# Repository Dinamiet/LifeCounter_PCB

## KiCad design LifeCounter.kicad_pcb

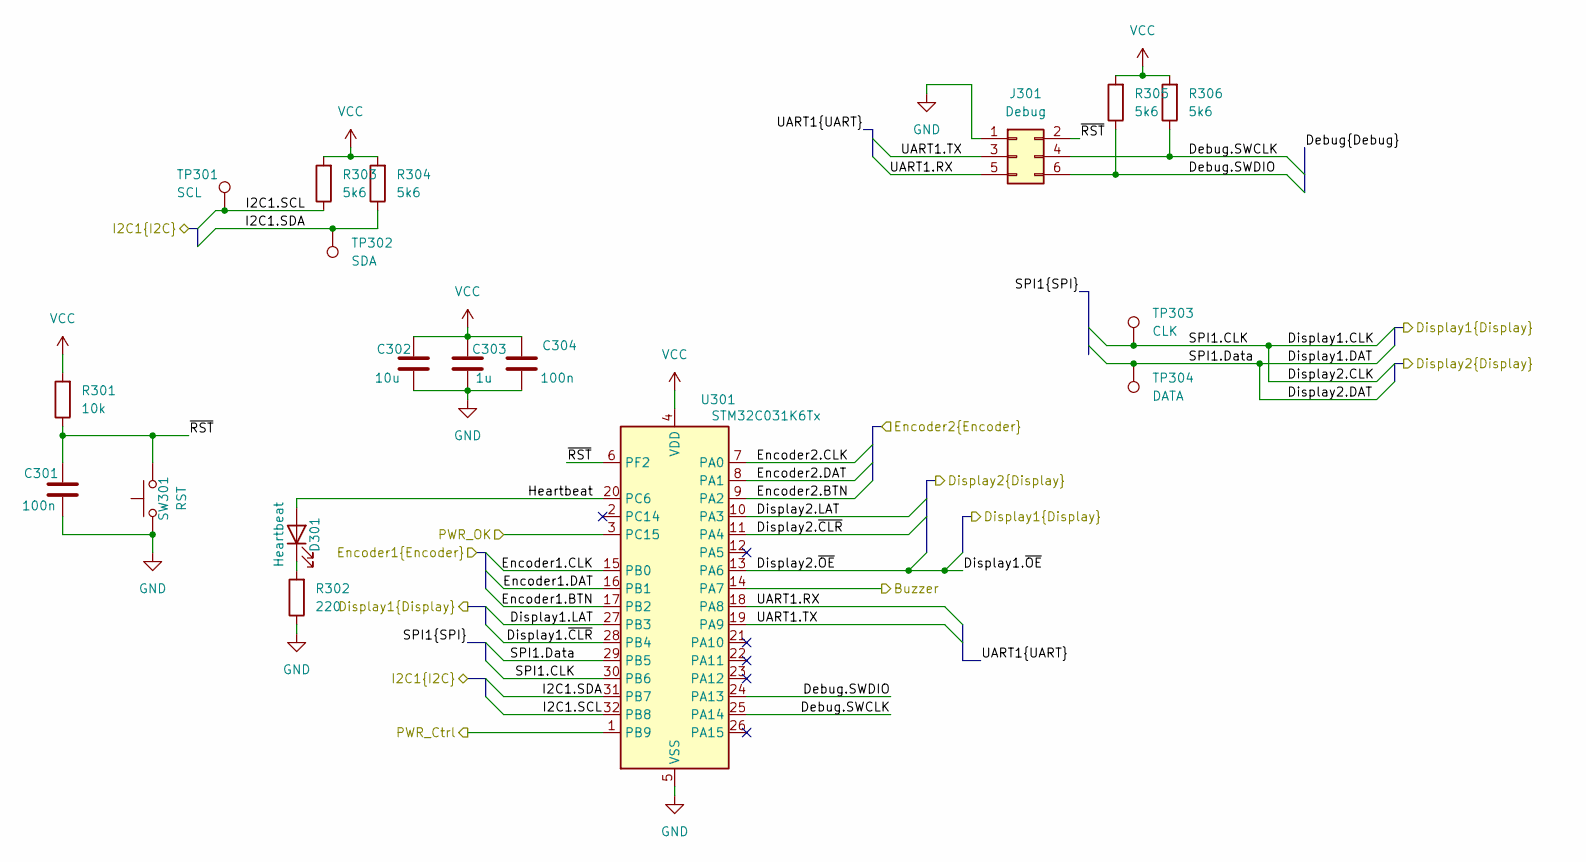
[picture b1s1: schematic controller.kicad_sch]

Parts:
C301, C304: 100n; C_1206_3216Metric_Pad1.33x1.80mm_HandSolder
C302: 10u; C_1206_3216Metric_Pad1.33x1.80mm_HandSolder
C303: 1u; C_0805_2012Metric_Pad1.18x1.45mm_HandSolder; LCSC C7393927
D301: Heartbeat; LED_1206_3216Metric_Pad1.42x1.75mm_HandSolder
J301: Debug; PinHeader_2x03_P2.54mm_Vertical_SMD
R301: 10k; R_1206_3216Metric_Pad1.30x1.75mm_HandSolder
R302: 220; R_1206_3216Metric_Pad1.30x1.75mm_HandSolder
R303, R304, R305, R306: 5k6; R_1206_3216Metric_Pad1.30x1.75mm_HandSolder
SW301: RST; SW_PUSH_6mm
TP301: SCL; TestPoint_Pad_D1.0mm
TP302: SDA; TestPoint_Pad_D1.0mm
TP303: CLK; TestPoint_Pad_D1.0mm
TP304: DATA; TestPoint_Pad_D1.0mm
U301: STM32C031K6Tx; LQFP-32_7x7mm_P0.8mm; LCSC C5456169

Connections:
/Buzzer/Buzz: U301.14 (PA7); also elsewhere on the board
/Controller/Debug.SWCLK: J301.4, R306.1, U301.25 (PA14)
/Controller/Debug.SWDIO: J301.6, R305.1, U301.24 (PA13)
/Controller/Encoder1.BTN: U301.17 (PB2); also elsewhere on the board
/Controller/Encoder1.CLK: U301.15 (PB0); also elsewhere on the board
/Controller/Encoder1.DAT: U301.16 (PB1); also elsewhere on the board
/Controller/Encoder2.BTN: U301.9 (PA2); also elsewhere on the board
/Controller/Encoder2.CLK: U301.7 (PA0); also elsewhere on the board
/Controller/Encoder2.DAT: U301.8 (PA1); also elsewhere on the board
/Controller/Heartbeat: D301.2 (A), U301.20 (PC6)
/Controller/I2C1.SCL: R303.1, TP301.1, U301.32 (PB8); also elsewhere on the board
/Controller/I2C1.SDA: R304.1, TP302.1, U301.31 (PB7); also elsewhere on the board
/Controller/PWR_Ctrl: U301.1 (PB9); also elsewhere on the board
/Controller/PWR_OK: U301.3 (PC15); also elsewhere on the board
/Controller/UART1.RX: J301.5, U301.18 (PA8)
/Controller/UART1.TX: J301.3, U301.19 (PA9)
/Controller/~RST: C301.1, J301.2, R301.1, SW301.2, U301.6 (PF2)
/Display1/CLK: TP303.1, U301.30 (PB6); also elsewhere on the board
/Display1/DAT: TP304.1, U301.29 (PB5); also elsewhere on the board
/Display1/LAT: U301.27 (PB3); also elsewhere on the board
/Display1/~CLR: U301.28 (PB4); also elsewhere on the board
/Display1/~OE: U301.13 (PA6); also elsewhere on the board
/Display2/LAT: U301.10 (PA3); also elsewhere on the board
/Display2/~CLR: U301.11 (PA4); also elsewhere on the board
GND: C301.2, C302.2, C303.2, C304.2, J301.1, R302.1, SW301.1, U301.5 (VSS); also elsewhere on the board
unnamed: D301.1 (K), R302.2
VCC: C302.1, C303.1, C304.1, R301.2, R303.2, R304.2, R305.2, R306.2, U301.4 (VDD); also elsewhere on the board

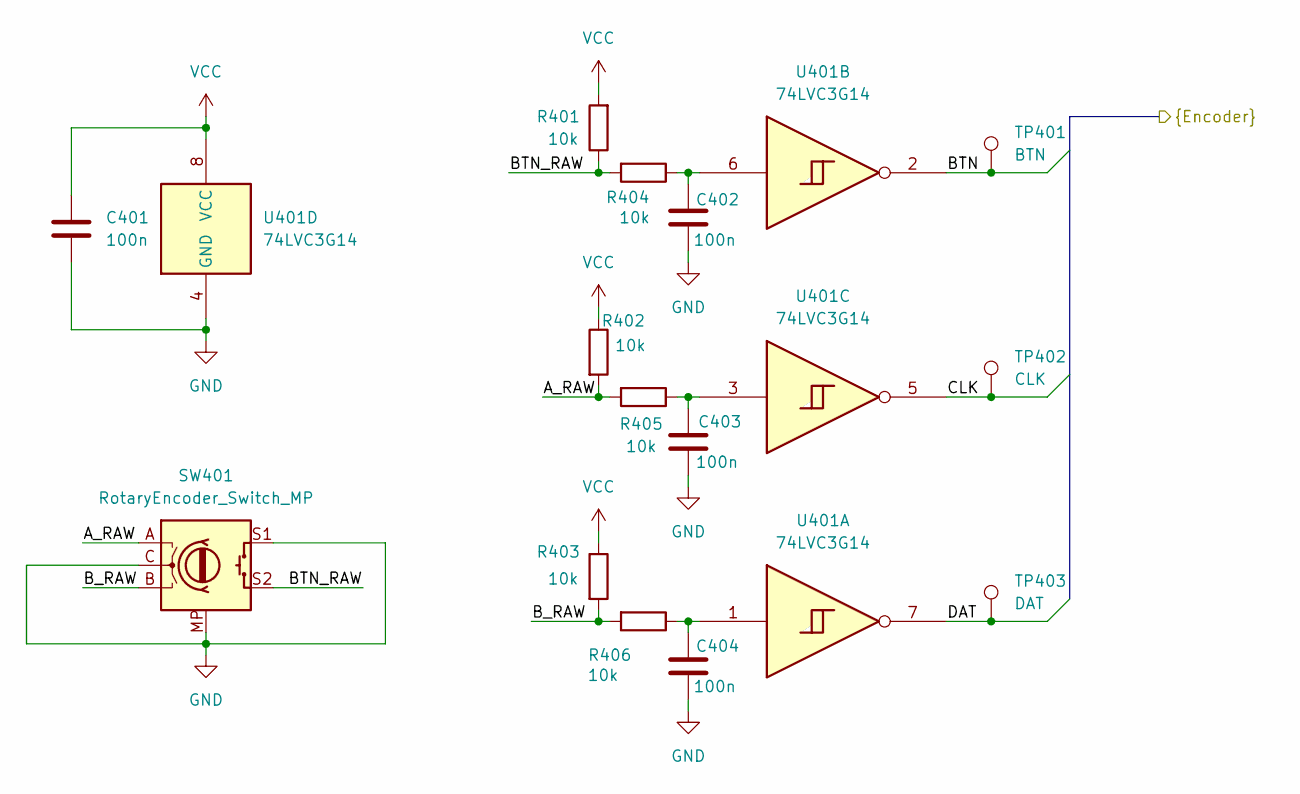
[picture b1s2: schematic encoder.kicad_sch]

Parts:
C401, C402, C403, C404: 100n; C_1206_3216Metric_Pad1.33x1.80mm_HandSolder
R401, R402, R403, R404, R405, R406: 10k; R_1206_3216Metric_Pad1.30x1.75mm_HandSolder
SW401: RotaryEncoder_Switch_MP; RotaryEncoder_Alps_EC12E-Switch_Vertical_H20mm; LCSC C470596
TP401: BTN; TestPoint_Pad_D1.0mm
TP402: CLK; TestPoint_Pad_D1.0mm
TP403: DAT; TestPoint_Pad_D1.0mm
U401: 74LVC3G14; VSSOP-8_2.3x2mm_P0.5mm; LCSC C98856

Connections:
/Controller/Encoder1.BTN: TP401.1, U401.2; also elsewhere on the board
/Controller/Encoder1.CLK: TP402.1, U401.5; also elsewhere on the board
/Controller/Encoder1.DAT: TP403.1, U401.7; also elsewhere on the board
/Encoder1/A_RAW: R402.2, R405.2, SW401.A
/Encoder1/BTN_RAW: R401.1, R404.2, SW401.S2
/Encoder1/B_RAW: R403.2, R406.2, SW401.B
GND: C401.2, C402.2, C403.2, C404.2, SW401.C, SW401.MP, SW401.S1, U401.4 (GND); also elsewhere on the board
unnamed: C402.1, R404.1, U401.6
unnamed: C403.1, R405.1, U401.3
unnamed: C404.1, R406.1, U401.1
VCC: C401.1, R401.2, R402.1, R403.1, U401.8 (VCC); also elsewhere on the board

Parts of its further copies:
C501, C502, C503, C504: 100n; C_1206_3216Metric_Pad1.33x1.80mm_HandSolder
R501, R502, R503, R504, R505, R506: 10k; R_1206_3216Metric_Pad1.30x1.75mm_HandSolder
SW501: RotaryEncoder_Switch_MP; RotaryEncoder_Alps_EC12E-Switch_Vertical_H20mm; LCSC C470596
TP501: BTN; TestPoint_Pad_D1.0mm
TP502: CLK; TestPoint_Pad_D1.0mm
TP503: DAT; TestPoint_Pad_D1.0mm
U501: 74LVC3G14; VSSOP-8_2.3x2mm_P0.5mm; LCSC C98856

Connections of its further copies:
/Controller/Encoder2.BTN: TP501.1, U501.2; also elsewhere on the board
/Controller/Encoder2.CLK: TP502.1, U501.5; also elsewhere on the board
/Controller/Encoder2.DAT: TP503.1, U501.7; also elsewhere on the board
/Encoder2/A_RAW: R502.2, R505.2, SW501.A
/Encoder2/BTN_RAW: R501.1, R504.2, SW501.S2
/Encoder2/B_RAW: R503.2, R506.2, SW501.B
GND: C501.2, C502.2, C503.2, C504.2, SW501.C, SW501.MP, SW501.S1, U501.4 (GND); also elsewhere on the board
unnamed: C502.1, R504.1, U501.6
unnamed: C503.1, R505.1, U501.3
unnamed: C504.1, R506.1, U501.1
VCC: C501.1, R501.2, R502.1, R503.1, U501.8 (VCC); also elsewhere on the board

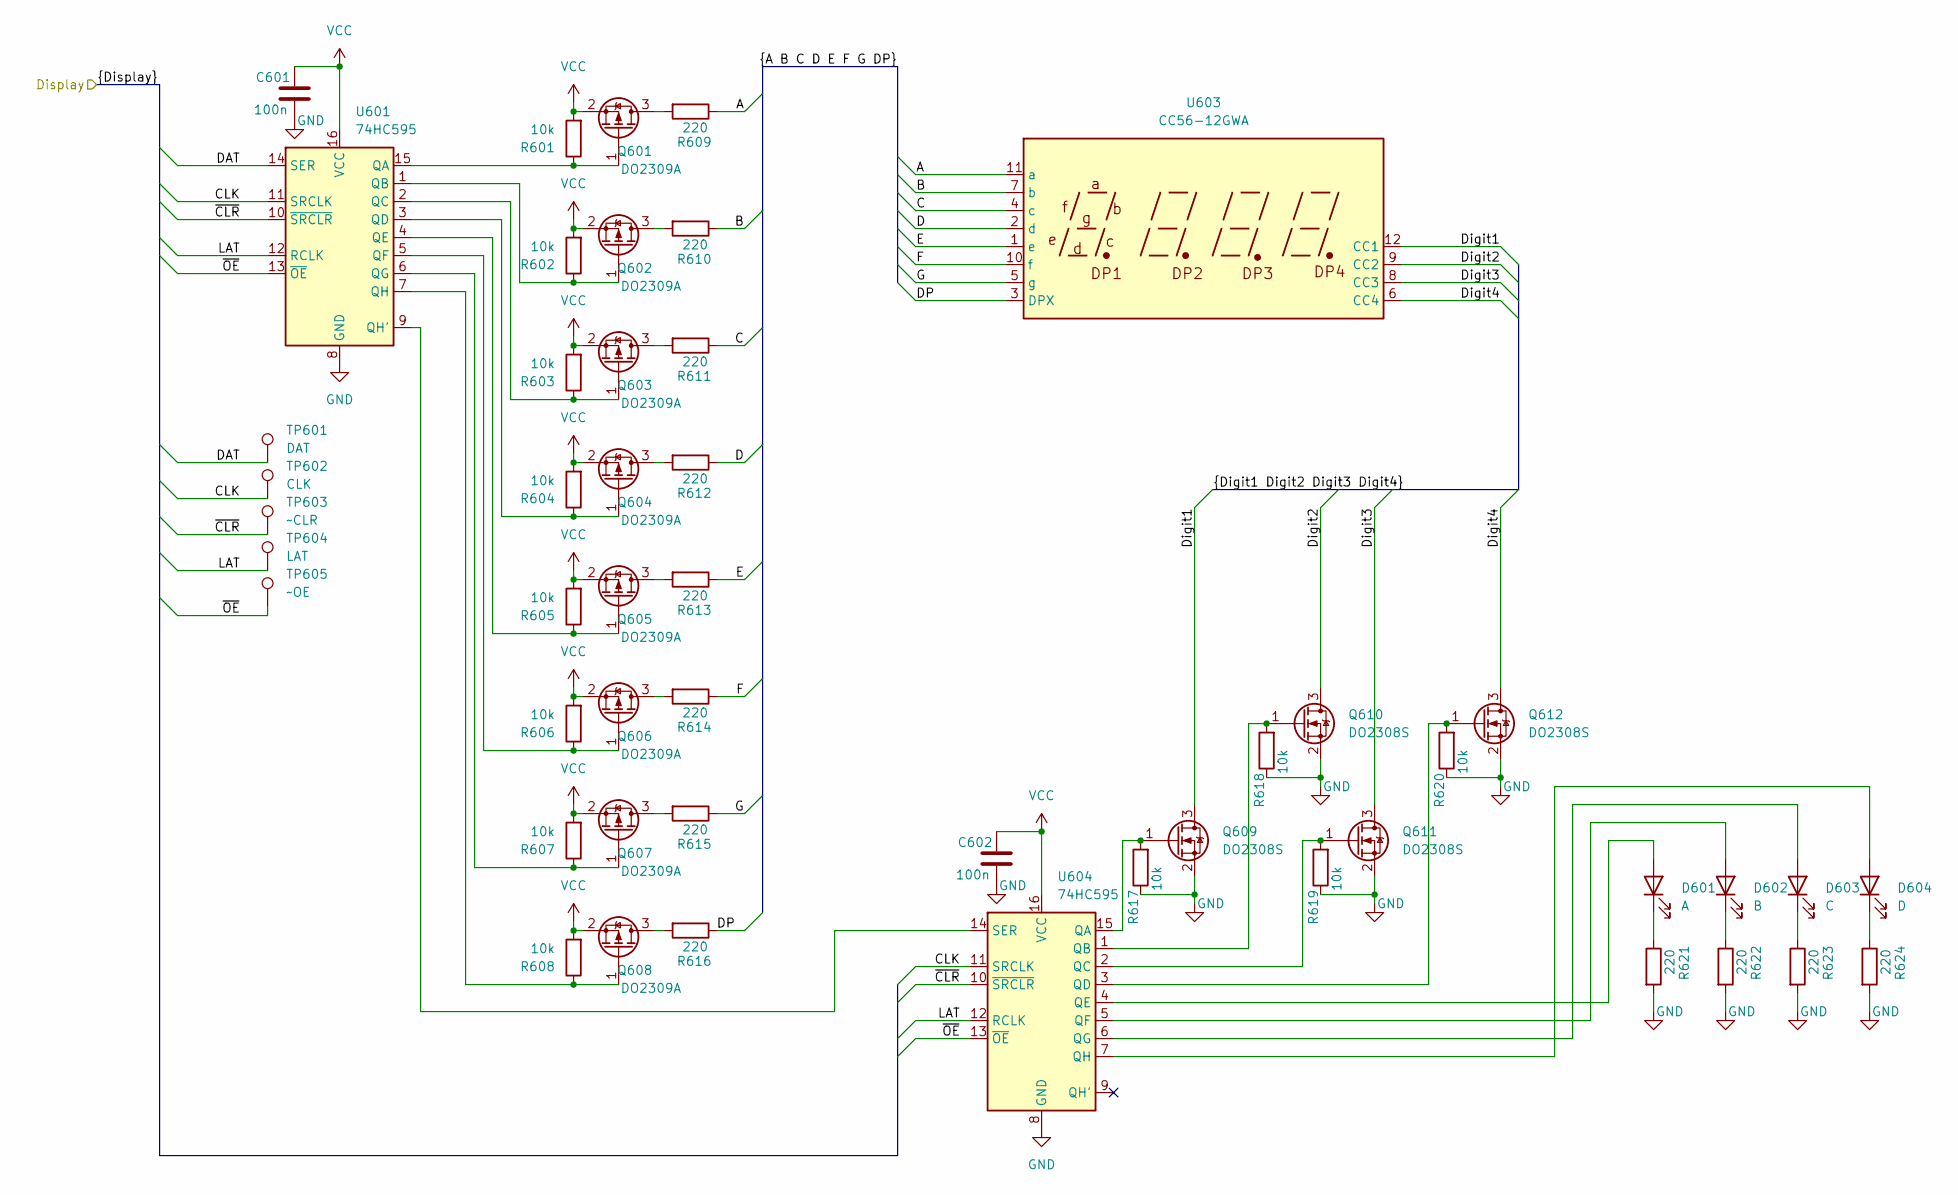
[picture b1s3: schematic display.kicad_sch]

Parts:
C601, C602: 100n; C_1206_3216Metric_Pad1.33x1.80mm_HandSolder
D601: A; LED_1206_3216Metric_Pad1.42x1.75mm_HandSolder
D602: B; LED_1206_3216Metric_Pad1.42x1.75mm_HandSolder
D603: C; LED_1206_3216Metric_Pad1.42x1.75mm_HandSolder
D604: D; LED_1206_3216Metric_Pad1.42x1.75mm_HandSolder
Q601, Q602, Q603, Q604, Q605, Q606, Q607, Q608: DO2309A; SOT-23_Handsoldering; LCSC C47018570
Q609, Q610, Q611, Q612: DO2308S; SOT-23_Handsoldering; LCSC C47018572
R601, R602, R603, R604, R605, R606, R607, R608, R617, R618, R619, R620: 10k; R_1206_3216Metric_Pad1.30x1.75mm_HandSolder
R609, R610, R611, R612, R613, R614, R615, R616, R621, R622, R623, R624: 220; R_1206_3216Metric_Pad1.30x1.75mm_HandSolder
TP601: DAT; TestPoint_Pad_D1.0mm
TP602: CLK; TestPoint_Pad_D1.0mm
TP603: ~CLR; TestPoint_Pad_D1.0mm
TP604: LAT; TestPoint_Pad_D1.0mm
TP605: ~OE; TestPoint_Pad_D1.0mm
U601, U604: 74HC595; SOIC-16_3.9x9.9mm_P1.27mm; LCSC C10092
U603: CC56-12GWA; LCSC C109200

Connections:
/Display1/A: R609.1, U603.11 (a)
/Display1/B: R610.1, U603.7 (b)
/Display1/C: R611.1, U603.4 (c)
/Display1/CLK: TP602.1, U601.11 (SRCLK), U604.11 (SRCLK); also elsewhere on the board
/Display1/D: R612.1, U603.2 (d)
/Display1/DAT: TP601.1, U601.14 (SER); also elsewhere on the board
/Display1/DP: R616.1, U603.3 (DPX)
/Display1/Digit1: Q609.3 (D), U603.12 (CC1)
/Display1/Digit2: Q610.3 (D), U603.9 (CC2)
/Display1/Digit3: Q611.3 (D), U603.8 (CC3)
/Display1/Digit4: Q612.3 (D), U603.6 (CC4)
/Display1/E: R613.1, U603.1 (e)
/Display1/F: R614.1, U603.10 (f)
/Display1/G: R615.1, U603.5 (g)
/Display1/LAT: TP604.1, U601.12 (RCLK), U604.12 (RCLK); also elsewhere on the board
/Display1/~CLR: TP603.1, U601.10 (~SRCLR), U604.10 (~SRCLR); also elsewhere on the board
/Display1/~OE: TP605.1, U601.13 (~OE), U604.13 (~OE); also elsewhere on the board
GND: C601.2, C602.2, Q609.2 (S), Q610.2 (S), Q611.2 (S), Q612.2 (S), R617.1, R618.1, R619.1, R620.1, R621.2, R622.2, R623.2, R624.2, U601.8 (GND), U604.8 (GND); also elsewhere on the board
unnamed: D601.2 (A), U604.4 (QE)
unnamed: D601.1 (K), R621.1
unnamed: D602.2 (A), U604.5 (QF)
unnamed: D602.1 (K), R622.1
unnamed: D603.2 (A), U604.6 (QG)
unnamed: D603.1 (K), R623.1
unnamed: D604.2 (A), U604.7 (QH)
unnamed: D604.1 (K), R624.1
unnamed: Q601.3 (D), R609.2
unnamed: Q601.1 (G), R601.1, U601.15 (QA)
unnamed: Q602.3 (D), R610.2
unnamed: Q602.1 (G), R602.1, U601.1 (QB)
unnamed: Q603.3 (D), R611.2
unnamed: Q603.1 (G), R603.1, U601.2 (QC)
unnamed: Q604.3 (D), R612.2
unnamed: Q604.1 (G), R604.1, U601.3 (QD)
unnamed: Q605.3 (D), R613.2
unnamed: Q605.1 (G), R605.1, U601.4 (QE)
unnamed: Q606.3 (D), R614.2
unnamed: Q606.1 (G), R606.1, U601.5 (QF)
unnamed: Q607.3 (D), R615.2
unnamed: Q607.1 (G), R607.1, U601.6 (QG)
unnamed: Q608.3 (D), R616.2
unnamed: Q608.1 (G), R608.1, U601.7 (QH)
unnamed: Q609.1 (G), R617.2, U604.15 (QA)
unnamed: Q610.1 (G), R618.2, U604.1 (QB)
unnamed: Q611.1 (G), R619.2, U604.2 (QC)
unnamed: Q612.1 (G), R620.2, U604.3 (QD)
unnamed: U601.9 (QH'), U604.14 (SER)
VCC: C601.1, C602.1, Q601.2 (S), Q602.2 (S), Q603.2 (S), Q604.2 (S), Q605.2 (S), Q606.2 (S), Q607.2 (S), Q608.2 (S), R601.2, R602.2, R603.2, R604.2, R605.2, R606.2, R607.2, R608.2, U601.16 (VCC), U604.16 (VCC); also elsewhere on the board

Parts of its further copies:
C701, C702: 100n; C_1206_3216Metric_Pad1.33x1.80mm_HandSolder
D701: A; LED_1206_3216Metric_Pad1.42x1.75mm_HandSolder
D702: B; LED_1206_3216Metric_Pad1.42x1.75mm_HandSolder
D703: C; LED_1206_3216Metric_Pad1.42x1.75mm_HandSolder
D704: D; LED_1206_3216Metric_Pad1.42x1.75mm_HandSolder
Q701, Q702, Q703, Q704, Q705, Q706, Q707, Q708: DO2309A; SOT-23_Handsoldering; LCSC C47018570
Q709, Q710, Q711, Q712: DO2308S; SOT-23_Handsoldering; LCSC C47018572
R701, R702, R703, R704, R705, R706, R707, R708, R717, R718, R719, R720: 10k; R_1206_3216Metric_Pad1.30x1.75mm_HandSolder
R709, R710, R711, R712, R713, R714, R715, R716, R721, R722, R723, R724: 220; R_1206_3216Metric_Pad1.30x1.75mm_HandSolder
TP701: DAT; TestPoint_Pad_D1.0mm
TP702: CLK; TestPoint_Pad_D1.0mm
TP703: ~CLR; TestPoint_Pad_D1.0mm
TP704: LAT; TestPoint_Pad_D1.0mm
TP705: ~OE; TestPoint_Pad_D1.0mm
U701, U704: 74HC595; SOIC-16_3.9x9.9mm_P1.27mm; LCSC C10092
U703: CC56-12GWA; LCSC C109200

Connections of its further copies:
/Display1/CLK: TP702.1, U701.11 (SRCLK), U704.11 (SRCLK); also elsewhere on the board
/Display1/DAT: TP701.1, U701.14 (SER); also elsewhere on the board
/Display1/~OE: TP705.1, U701.13 (~OE), U704.13 (~OE); also elsewhere on the board
/Display2/A: R709.1, U703.11 (a)
/Display2/B: R710.1, U703.7 (b)
/Display2/C: R711.1, U703.4 (c)
/Display2/D: R712.1, U703.2 (d)
/Display2/DP: R716.1, U703.3 (DPX)
/Display2/Digit1: Q709.3 (D), U703.12 (CC1)
/Display2/Digit2: Q710.3 (D), U703.9 (CC2)
/Display2/Digit3: Q711.3 (D), U703.8 (CC3)
/Display2/Digit4: Q712.3 (D), U703.6 (CC4)
/Display2/E: R713.1, U703.1 (e)
/Display2/F: R714.1, U703.10 (f)
/Display2/G: R715.1, U703.5 (g)
/Display2/LAT: TP704.1, U701.12 (RCLK), U704.12 (RCLK); also elsewhere on the board
/Display2/~CLR: TP703.1, U701.10 (~SRCLR), U704.10 (~SRCLR); also elsewhere on the board
GND: C701.2, C702.2, Q709.2 (S), Q710.2 (S), Q711.2 (S), Q712.2 (S), R717.1, R718.1, R719.1, R720.1, R721.2, R722.2, R723.2, R724.2, U701.8 (GND), U704.8 (GND); also elsewhere on the board
unnamed: D701.2 (A), U704.4 (QE)
unnamed: D701.1 (K), R721.1
unnamed: D702.2 (A), U704.5 (QF)
unnamed: D702.1 (K), R722.1
unnamed: D703.2 (A), U704.6 (QG)
unnamed: D703.1 (K), R723.1
unnamed: D704.2 (A), U704.7 (QH)
unnamed: D704.1 (K), R724.1
unnamed: Q701.3 (D), R709.2
unnamed: Q701.1 (G), R701.1, U701.15 (QA)
unnamed: Q702.3 (D), R710.2
unnamed: Q702.1 (G), R702.1, U701.1 (QB)
unnamed: Q703.3 (D), R711.2
unnamed: Q703.1 (G), R703.1, U701.2 (QC)
unnamed: Q704.3 (D), R712.2
unnamed: Q704.1 (G), R704.1, U701.3 (QD)
unnamed: Q705.3 (D), R713.2
unnamed: Q705.1 (G), R705.1, U701.4 (QE)
unnamed: Q706.3 (D), R714.2
unnamed: Q706.1 (G), R706.1, U701.5 (QF)
unnamed: Q707.3 (D), R715.2
unnamed: Q707.1 (G), R707.1, U701.6 (QG)
unnamed: Q708.3 (D), R716.2
unnamed: Q708.1 (G), R708.1, U701.7 (QH)
unnamed: Q709.1 (G), R717.2, U704.15 (QA)
unnamed: Q710.1 (G), R718.2, U704.1 (QB)
unnamed: Q711.1 (G), R719.2, U704.2 (QC)
unnamed: Q712.1 (G), R720.2, U704.3 (QD)
unnamed: U701.9 (QH'), U704.14 (SER)
VCC: C701.1, C702.1, Q701.2 (S), Q702.2 (S), Q703.2 (S), Q704.2 (S), Q705.2 (S), Q706.2 (S), Q707.2 (S), Q708.2 (S), R701.2, R702.2, R703.2, R704.2, R705.2, R706.2, R707.2, R708.2, U701.16 (VCC), U704.16 (VCC); also elsewhere on the board

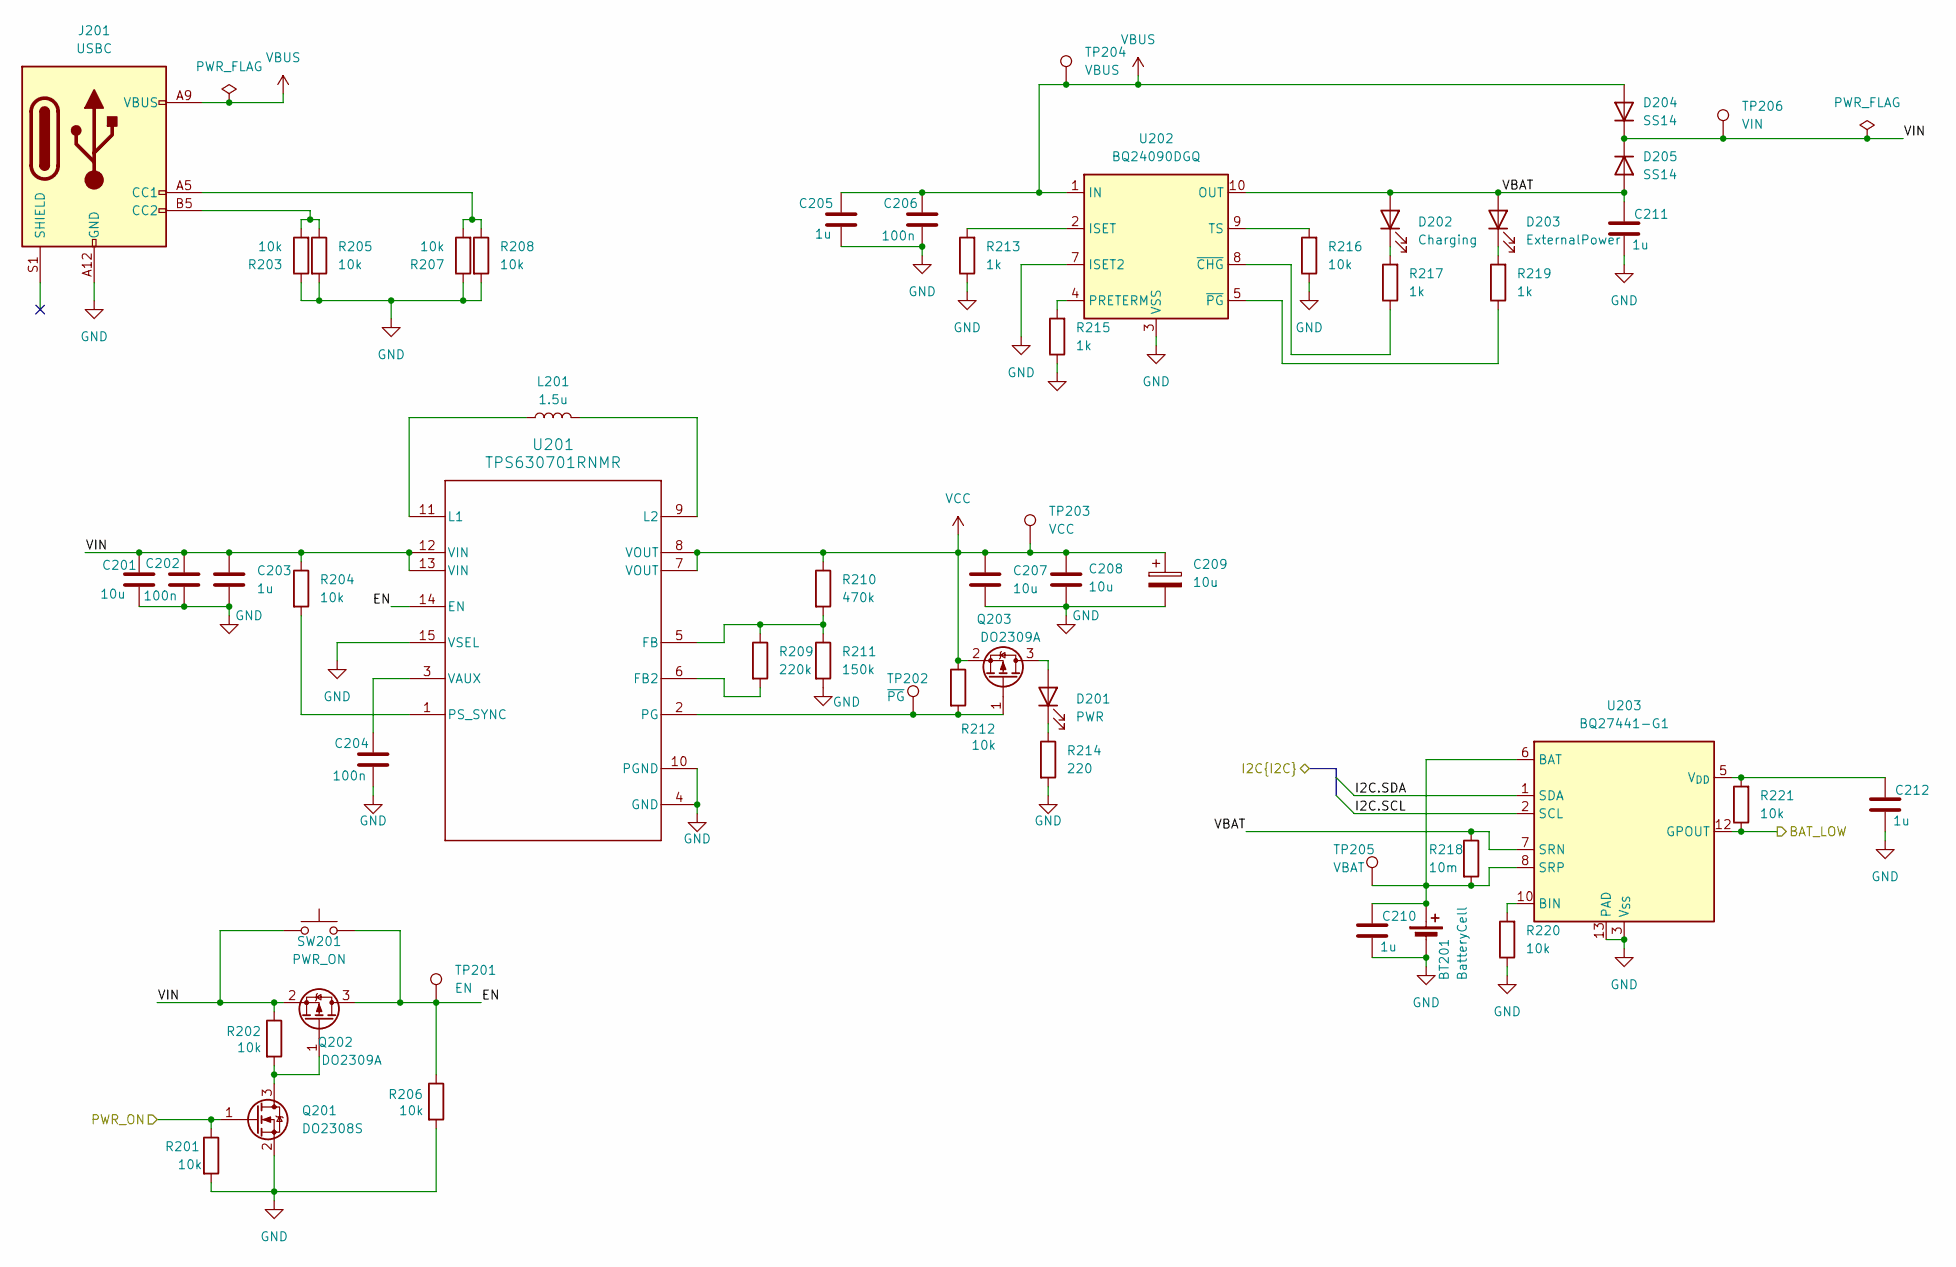
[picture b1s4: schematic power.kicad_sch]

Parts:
BT201: BatteryCell; BatteryHolder_MPD_BH-18650-PC; LCSC C5290175
C201, C207, C208: 10u; C_1206_3216Metric_Pad1.33x1.80mm_HandSolder
C202, C204, C206: 100n; C_1206_3216Metric_Pad1.33x1.80mm_HandSolder
C203, C205, C210, C211, C212: 1u; C_0805_2012Metric_Pad1.18x1.45mm_HandSolder; LCSC C7393927
C209: 10u; CP_EIA-7343-31_Kemet-D_HandSolder
D201: PWR; LED_1206_3216Metric_Pad1.42x1.75mm_HandSolder
D202: Charging; LED_1206_3216Metric_Pad1.42x1.75mm_HandSolder
D203: ExternalPower; LED_1206_3216Metric_Pad1.42x1.75mm_HandSolder
D204, D205: SS14; D_SMA_Handsoldering; LCSC C2986110
J201: USBC; USB_C_Receptacle_GCT_USB4125-xx-x_6P_TopMnt_Horizontal; LCSC C42400234
L201: 1.5u; L_Cenker_CKCS4020; LCSC C5442006
Q201: DO2308S; SOT-23_Handsoldering; LCSC C47018572
Q202, Q203: DO2309A; SOT-23_Handsoldering; LCSC C47018570
R201, R202, R203, R204, R205, R206, R207, R208, R212, R216, R220, R221: 10k; R_1206_3216Metric_Pad1.30x1.75mm_HandSolder
R209: 220k; R_0805_2012Metric_Pad1.20x1.40mm_HandSolder; LCSC C5140137
R210: 470k; R_0805_2012Metric_Pad1.20x1.40mm_HandSolder; LCSC C3016836
R211: 150k; R_0805_2012Metric_Pad1.20x1.40mm_HandSolder; LCSC C365243
R213, R215, R217, R219: 1k; R_1206_3216Metric_Pad1.30x1.75mm_HandSolder
R214: 220; R_1206_3216Metric_Pad1.30x1.75mm_HandSolder
R218: 10m; R_0805_2012Metric_Pad1.20x1.40mm_HandSolder; LCSC C2961480
SW201: PWR_ON; SW_PUSH_6mm
TP201: EN; TestPoint_Pad_D1.0mm
TP202: ~{PG}; TestPoint_Pad_D1.0mm
TP203: VCC; TestPoint_Pad_D1.0mm
TP204: VBUS; TestPoint_Pad_D1.0mm
TP205: VBAT; TestPoint_Pad_D1.0mm
TP206: VIN; TestPoint_Pad_D1.0mm
U201: TPS630701RNMR; TPS63070; LCSC C109322
U202: BQ24090DGQ; HVSSOP-10-1EP_3x3mm_P0.5mm_EP1.57x1.88mm; LCSC C43306
U203: BQ27441-G1; Texas_S-PDSO-N12; LCSC C2864880

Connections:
/Controller/I2C1.SCL: U203.2 (SCL); also elsewhere on the board
/Controller/I2C1.SDA: U203.1 (SDA); also elsewhere on the board
/Controller/PWR_Ctrl: Q201.1 (G), R201.1; also elsewhere on the board
/Controller/PWR_OK: R221.1, U203.12 (GPOUT); also elsewhere on the board
/Power/EN: Q202.3 (D), R206.1, SW201.2, TP201.1, U201.14 (EN)
/Power/VBAT: C211.1, D202.2 (A), D203.2 (A), D205.2 (A), R218.1, U202.10 (OUT), U203.7 (SRN)
/Power/VIN: C201.1, C202.1, C203.1, D204.1 (K), D205.1 (K), Q202.2 (S), R202.1, R204.1, SW201.1, TP206.1, U201.12 (VIN), U201.13 (VIN)
GND: BT201.2 (-), C201.2, C202.2, C203.2, C204.2, C205.2, C206.2, C207.2, C208.2, C209.2, C210.2, C211.2, C212.2, J201.A12 (GND), J201.B12 (GND), Q201.2 (S), R201.2, R203.1, R205.2, R206.2, R207.1, R208.2, R211.2, R213.1, R214.2, R215.1, R216.1, R220.1, U201.4 (GND), U201.10 (PGND), U201.15 (VSEL), U202.3 (VSS), U202.7 (ISET2), U202.11 (VSS), U203.3 (V_{SS}), U203.13 (PAD); also elsewhere on the board
unnamed: BT201.1 (+), C210.1, R218.2, TP205.1, U203.6 (BAT), U203.8 (SRP)
unnamed: D201.2 (A), Q203.3 (D)
unnamed: D201.1 (K), R214.1
unnamed: D202.1 (K), R217.2
unnamed: D203.1 (K), R219.2
unnamed: J201.A5 (CC1), R207.2, R208.1
unnamed: J201.B5 (CC2), R203.2, R205.1
unnamed: Q201.3 (D), Q202.1 (G), R202.2
unnamed: Q203.1 (G), R212.2, TP202.1, U201.2 (PG)
unnamed: R209.2, U201.6 (FB2)
unnamed: R209.1, R210.2, R211.1, U201.5 (FB)
unnamed: L201.1, U201.11 (L1)
unnamed: L201.2, U201.9 (L2)
unnamed: R204.2, U201.1 (PS_SYNC)
unnamed: C204.1, U201.3 (VAUX)
unnamed: R213.2, U202.2 (ISET)
unnamed: R215.2, U202.4 (PRETERM)
unnamed: R216.2, U202.9 (TS)
unnamed: R217.1, U202.8 (~CHG)
unnamed: R219.1, U202.5 (~PG)
unnamed: R220.2, U203.10 (BIN)
unnamed: C212.1, R221.2, U203.5 (V_{DD})
VBUS: C205.1, C206.1, D204.2 (A), J201.A9 (VBUS), J201.B9 (VBUS), TP204.1, U202.1 (IN)
VCC: C207.1, C208.1, C209.1, Q203.2 (S), R210.1, R212.1, TP203.1, U201.7 (VOUT), U201.8 (VOUT); also elsewhere on the board

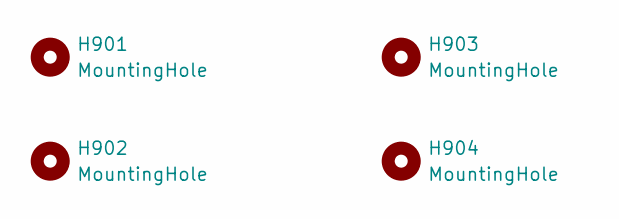
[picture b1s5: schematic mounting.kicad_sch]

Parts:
H901, H902, H903, H904: MountingHole; MountingHole_2mm

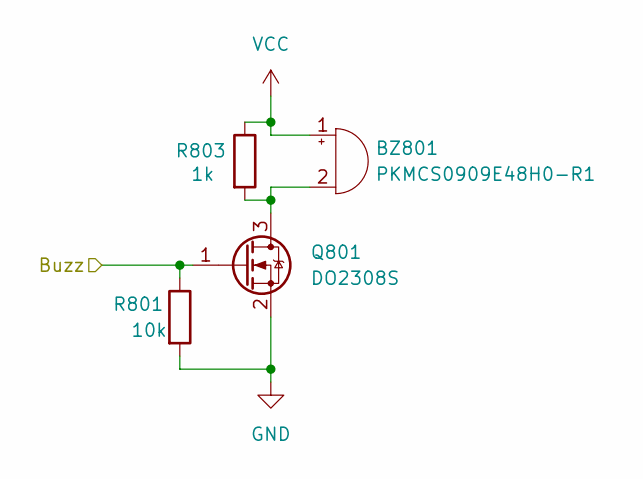
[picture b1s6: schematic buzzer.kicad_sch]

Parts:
BZ801: PKMCS0909E48H0-R1; Buzzer_12x9.5RM7.6
Q801: DO2308S; SOT-23_Handsoldering; LCSC C47018572
R801: 10k; R_1206_3216Metric_Pad1.30x1.75mm_HandSolder
R803: 1k; R_1206_3216Metric_Pad1.30x1.75mm_HandSolder

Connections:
/Buzzer/Buzz: Q801.1 (G), R801.1; also elsewhere on the board
GND: Q801.2 (S), R801.2; also elsewhere on the board
unnamed: BZ801.2 (-), Q801.3 (D), R803.2
VCC: BZ801.1 (+), R803.1; also elsewhere on the board

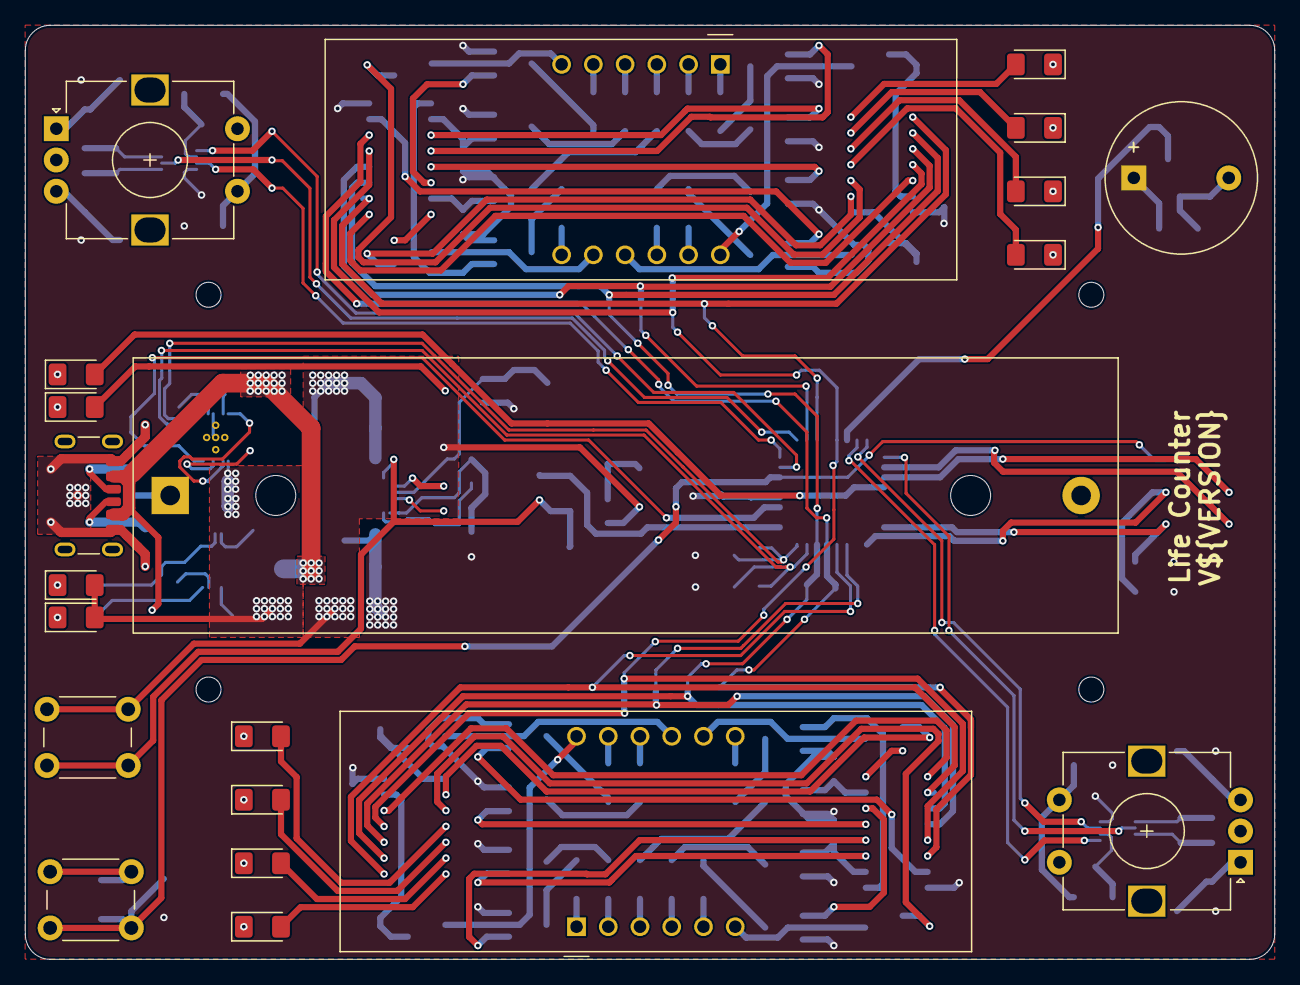
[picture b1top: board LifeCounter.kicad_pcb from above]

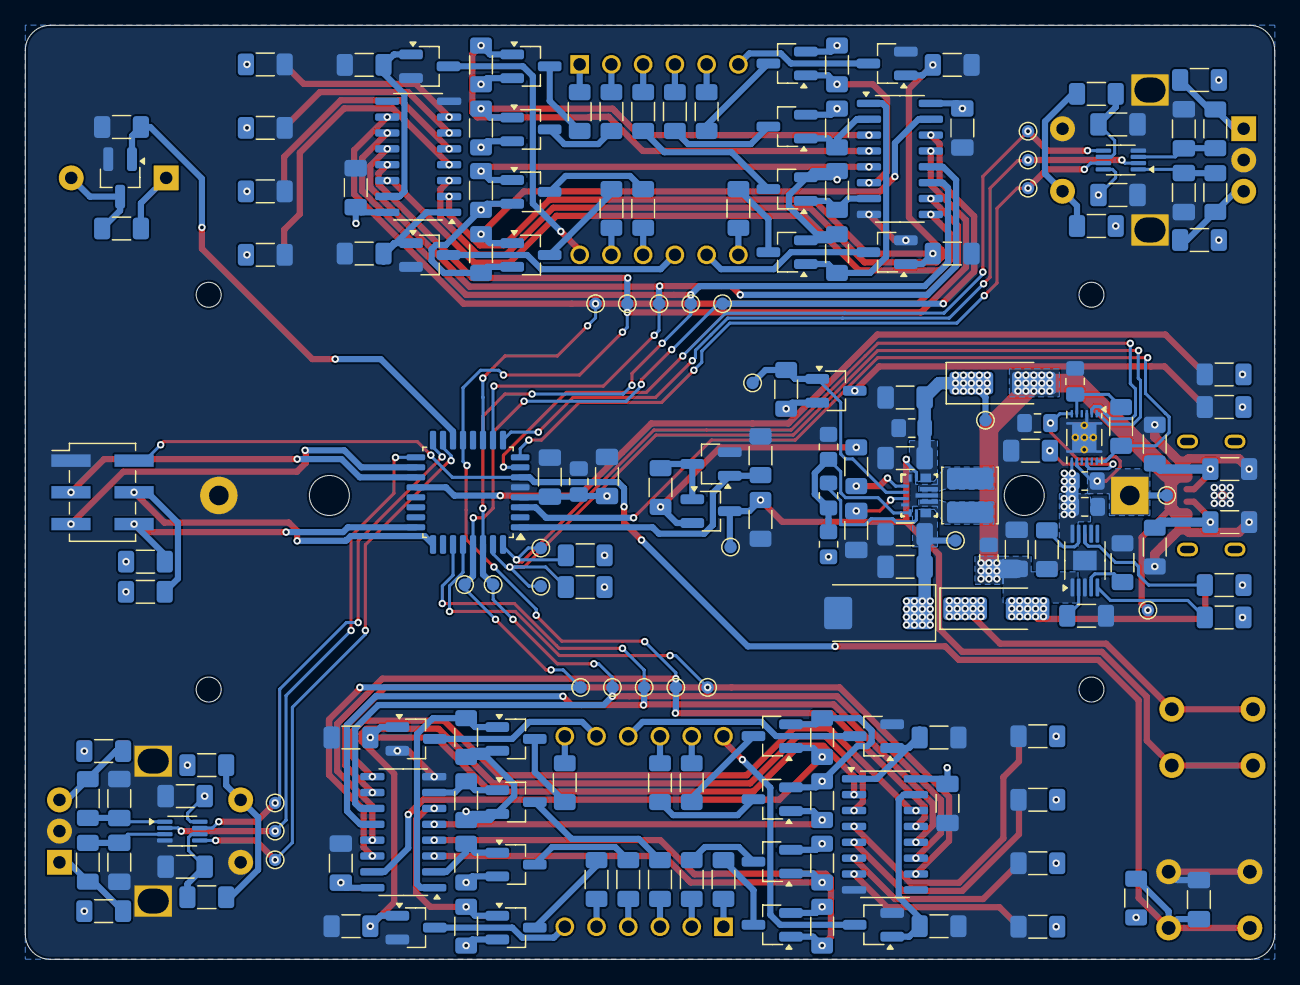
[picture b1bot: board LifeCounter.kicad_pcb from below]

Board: 2 copper layers, 100.0 x 74.8 mm, 210 parts (185 on the bottom side), 148 nets.

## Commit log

2024-12-23 Project creation
2024-12-23 Ignore extra KiCad files
2024-12-23 Display and Status circuits added
2024-12-24 Add encoders
2024-12-24 Add buzzer
2024-12-24 Split schematic into multiple sheets
2024-12-24 Rename
2024-12-25 Power layout
2024-12-25 Constant current sink status driver
2024-12-25 Controller selection
2025-01-10 Controller wiring and schematic semantics
2025-01-10 Add mounting holes
2025-01-10 Component hookup
2025-01-10 Decoupling caps for ICs
2025-01-10 LED descriptions - Status LEDs could use some more work
2025-01-10 Initial component placement
2025-01-18 Initial layout
2025-02-15 Switch transistors to FETs
2025-02-21 Constant current sink to status LEDs and rewiring controller
2025-03-14 Add GitHub Sponsor configuration
2025-04-04 Power control using p-channel for switching
2025-04-04 KiCAD version update
2025-04-05 Assign component values to display passives
2025-04-05 Status component value assignment
2025-04-05 Encoder component values
2025-04-05 Power component value assignment
2025-04-05 Buzzer component value assignment
2025-04-05 Controller component value assignment
2025-04-06 Decoupling capacitor change from 10u to 1u
2025-04-06 Resolve ERC warnings
2025-04-12 5k1 USB resistors
2025-04-12 Add Testpoints
2025-04-12 Footprint selection
2025-04-12 Library lookup
2025-04-21 Using Schmitt trigger for encoder debouncing
2025-04-22 Add funding configuration for GitHub
2025-04-22 Add decoupling capacitor to Schmitt trigger
2025-04-22 Clean layout
2025-04-23 Polarized Tantalum capacitor symbol
2025-04-23 Using larger footprint for Status LED driver
2025-04-23 Encoder bus names change
2025-04-23 Split encoder raw and filtered signal names
2025-04-23 USB 10k//10k CC resistors
2025-04-23 Initial component grouping and placement
2025-04-25 Update component footprint selection
2025-04-25 Organise subcircuit layouts
2025-04-26 Fix encoder debounce
2025-04-26 Initial board layout
2025-04-27 Update track constraints
2025-04-27 Started routing component blocks
2025-04-28 Fix controller encoder bus names
2025-04-28 Routing player status LEDs and display
2025-04-28 Center led driver
2025-04-28 Power routed
2025-04-28 Routed
2025-04-28 Fix some DRC errors, silkscreen overlaps and cutoffs still outstanding
2025-05-12 Selected buzzer components
2025-05-12 Use new regulator
2025-05-12 Buzzer using high switch
2025-05-12 Library rename and add buck-boost regulator
2025-05-12 Using buck-boost regulator
2025-05-12 Remove display and status for redo
2025-05-12 Shift register display and status
2025-05-13 Second display
2025-05-13 Reroute CPU for new display driving
2025-05-13 Connect displays to controller
2025-05-16 Page reordering
2025-06-10 Assign component LCSC part numbers
2025-06-11 New layout with updated constraints
2025-06-14 Simplify some schematics to reduce BOM
2025-06-14 Layout of display and power
2025-06-15 Subcircuits routed
2025-07-01 Swapped pins for user elements to make routing easier
2025-07-01 Fix unconnected pin
2025-07-01 Add log files to ignore
2025-07-01 Everything routed :)
2025-07-01 Move silkscreen text to comments layer
2025-07-03 Resolve DRC issues
2025-07-04 Rounded PCB corners
2025-07-04 Add version to silkscreen
2025-07-04 Plot settings updated
2025-07-05 Update BOM options for export
